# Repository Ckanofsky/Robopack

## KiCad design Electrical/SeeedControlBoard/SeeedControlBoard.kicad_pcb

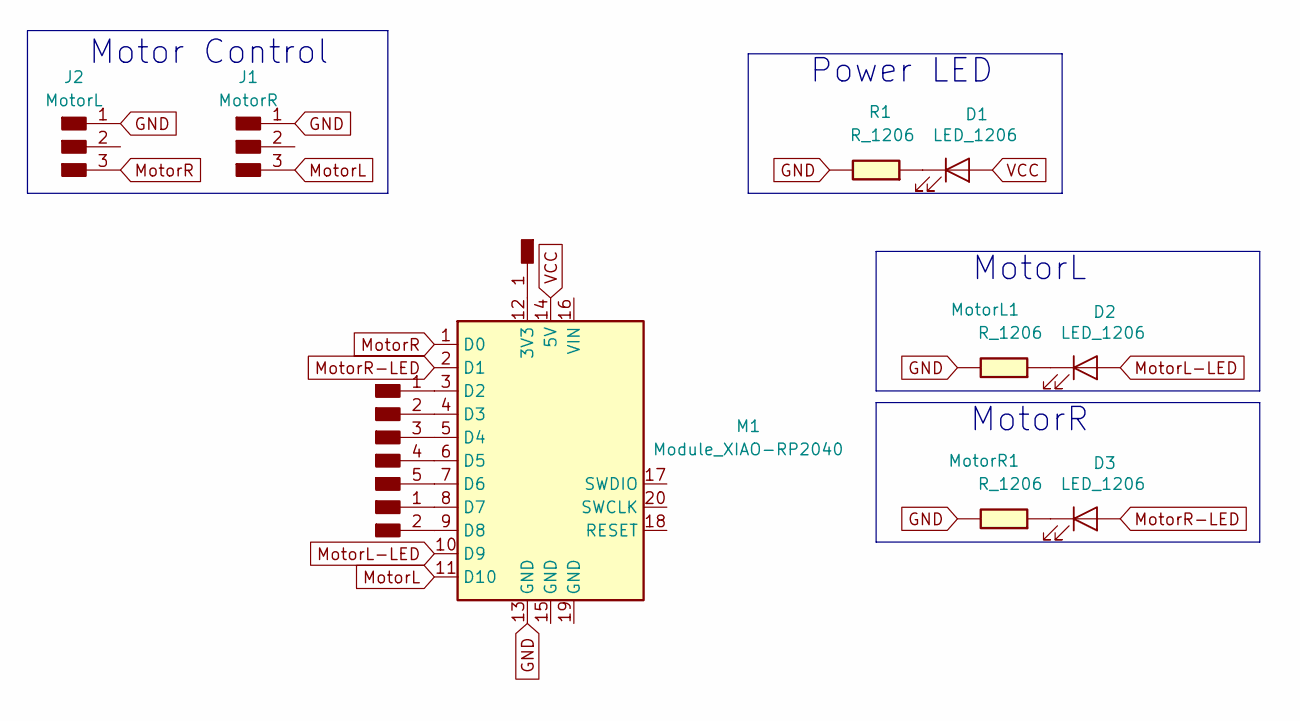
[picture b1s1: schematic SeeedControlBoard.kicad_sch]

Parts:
D1, D2, D3: LED_1206
J1: MotorR; PinHeader_1x03_P2.54mm_Vertical_THT_D1mm
J2: MotorL; PinHeader_1x03_P2.54mm_Vertical_THT_D1mm
J3: Conn_PinHeader_1x05_P2.54mm_Horizontal_SMD; PinHeader_1x05_P2.54mm_Horizontal_SMD
J4: Conn_PinHeader_1x02_P2.54mm_Horizontal_SMD; PinHeader_1x02_P2.54mm_Horizontal_SMD
J5: Conn_PinHeader_1x01_P2.54mm_Horizontal_SMD; PinHeader_1x01_P2.54mm_Horizontal_SMD
M1: Module_XIAO-RP2040; SeeedStudio_XIAO_RP2040
MotorL1: R_1206
MotorR1: R_1206
R1: R_1206

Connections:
GND: J1.1, J2.1, M1.13 (GND), MotorL1.1, MotorR1.1, R1.1
MotorL: J1.3, M1.11 (D10)
MotorL-LED: D2.2 (A), M1.10 (D9)
MotorR: J2.3, M1.1 (D0)
MotorR-LED: D3.2 (A), M1.2 (D1)
unnamed: D1.1 (K), R1.2
unnamed: D2.1 (K), MotorL1.2
unnamed: D3.1 (K), MotorR1.2
unnamed: J3.1, M1.3 (D2)
unnamed: J3.2, M1.4 (D3)
unnamed: J3.3, M1.5 (D4)
unnamed: J3.4, M1.6 (D5)
unnamed: J3.5, M1.7 (D6)
unnamed: J4.1, M1.8 (D7)
unnamed: J4.2, M1.9 (D8)
unnamed: J5.1, M1.12 (3V3)
VCC: D1.2 (A), M1.14 (5V)

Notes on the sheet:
MotorL
Motor Control
Power LED
MotorR

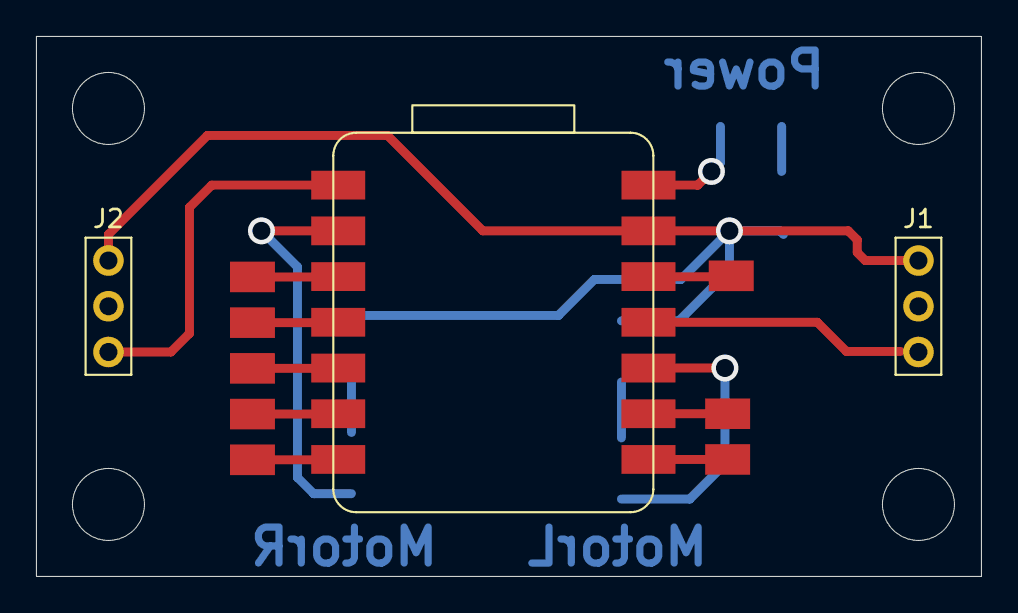
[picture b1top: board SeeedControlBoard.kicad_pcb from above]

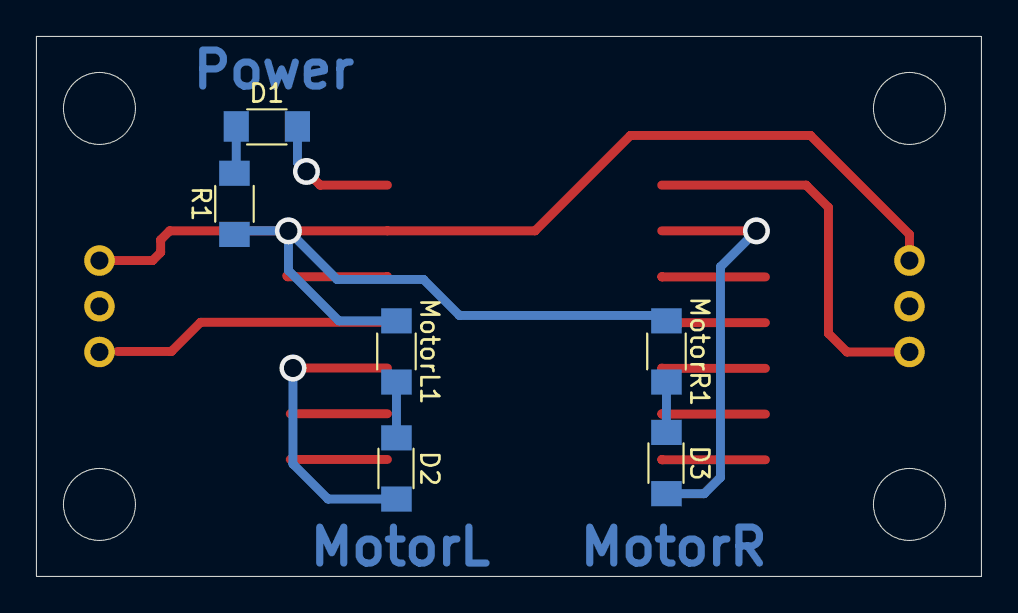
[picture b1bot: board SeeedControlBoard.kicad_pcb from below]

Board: 2 copper layers, 52.5 x 30.0 mm, 12 parts (6 on the bottom side), 17 nets.

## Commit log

2025-05-08 added human identify code
2025-05-09 Working Detection Code and Instructions - needs actual motor code
2026-04-01 the start
